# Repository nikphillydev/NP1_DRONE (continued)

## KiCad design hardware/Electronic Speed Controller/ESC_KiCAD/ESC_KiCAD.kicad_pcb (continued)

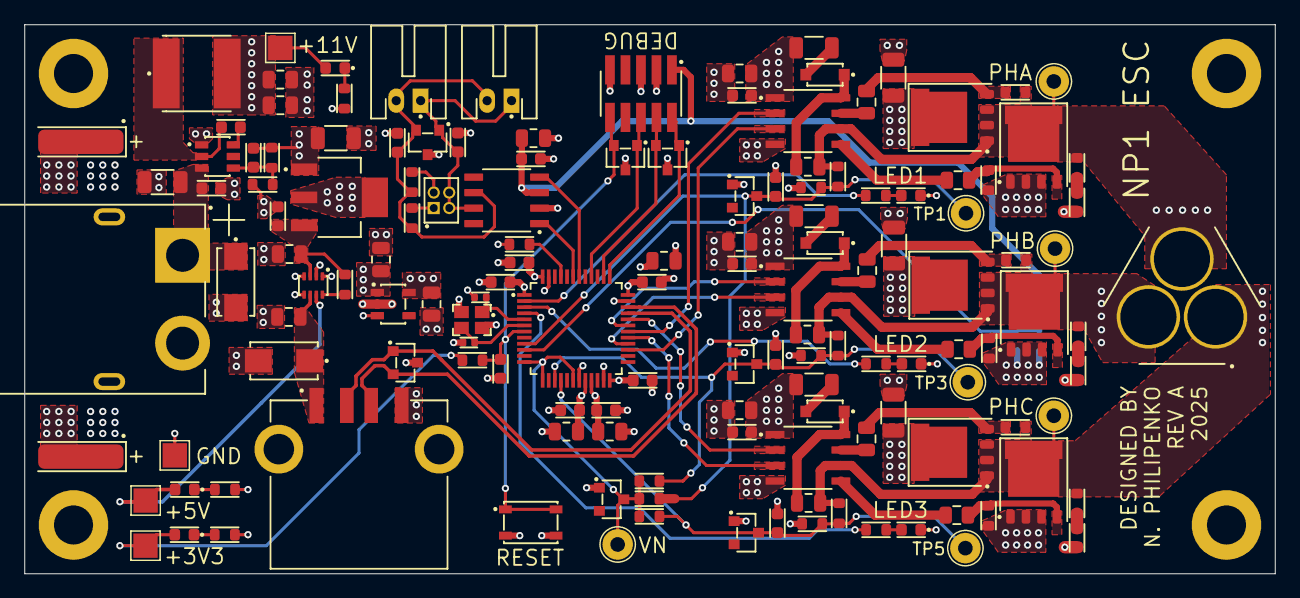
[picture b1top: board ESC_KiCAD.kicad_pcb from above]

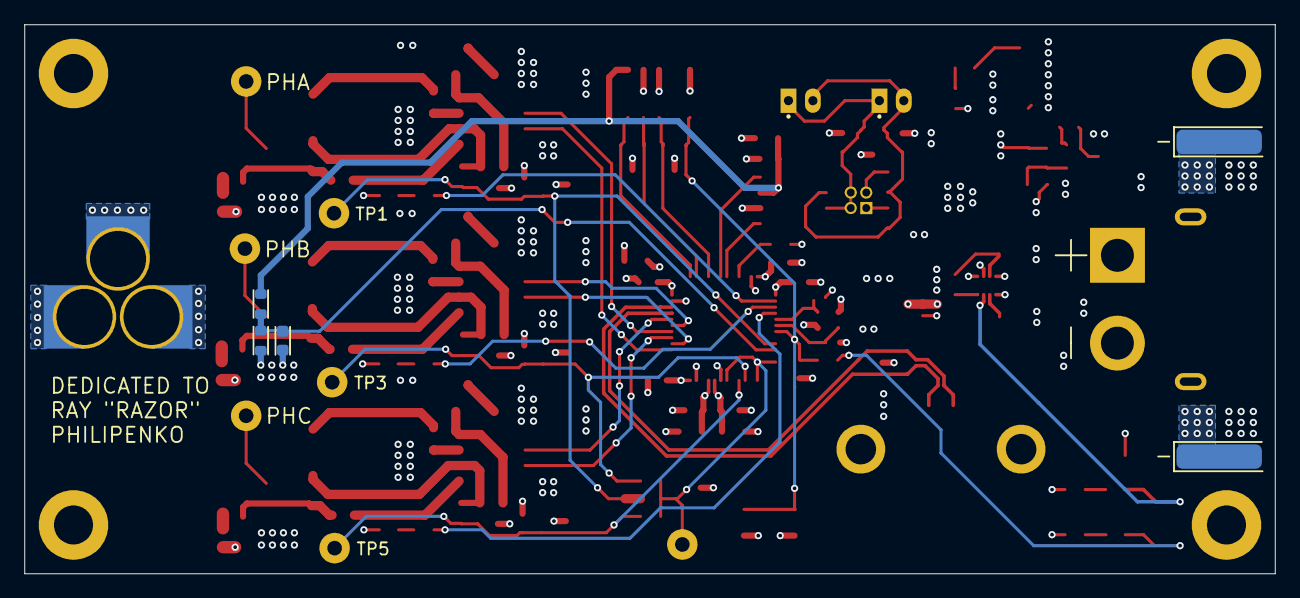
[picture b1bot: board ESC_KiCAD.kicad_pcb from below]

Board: 4 copper layers, 102.5 x 45.0 mm, 150 parts (3 on the bottom side), 70 nets.

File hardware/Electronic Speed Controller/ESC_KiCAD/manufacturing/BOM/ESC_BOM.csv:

"Reference","Value","Description","Qty","JLCPCB Part #","Manufacturer","Manufacturer Part #"
"C1,C8,C11,C17,C43","4.7uF","CAP CER 4.7UF 25V X5R 0805","5","C1779","Samsung Electro-Mechanics","CL21A475KAQNNNE"
"C2,C9,C12,C18,C27,C28,C31,C39,C42,C44,C45,C47,C49","100nF","CAP CER 0.1UF 50V X7R 0603","13","C14663","YAGEO","CC0603KRX7R9BB104"
"C3,C13,C19,C29,C30,C33,C36,C38,C40","1uF","CAP CER 1UF 50V X7R 0805","9","C28323","Samsung Electro-Mechanics","CL21B105KBFNNNE"
"C4,C5","47pF","CAP CER 47PF 50V C0G/NP0 0603","2","C1671","Samsung Electro-Mechanics","CL10C470JB8NNNC"
"C6,C14,C20,C23,C26","10uF","CAP CER 10UF 50V X5R 1206","5","C13585","Samsung Electro-Mechanics","CL31A106KBHNNNE"
"C7,C15,C21","1nF","CAP CER 1000PF 50V X7R 0603","3","C1588","Samsung Electro-Mechanics","CL10B102KB8NNNC"
"C10,C16,C22,C37,C41","10nF","CAP CER 10000PF 50V X7R 0603","5","C57112","Samsung Electro-Mechanics","CL10B103KB8NNNC"
"C24,C25","330uF","CAP ALUM 330UF 20% 35V RADIAL TH","2","C75177","Rubycon","35ZLH330MEFC10X12.5"
"C32","100pF","CAP CER 100PF 50V C0G/NP0 0603","1","C14858","Samsung Electro-Mechanics","CL10C101JB8NNNC"
"C34,C35","22uF","CAP CER 22UF 25V X5R 0805","2","C45783","Samsung Electro-Mechanics","CL21A226MAYNNNE"
"C46,C48","11pF","CAP CER 11PF 50V C0G/NP0 0402","2","C710643","Murata Electronics","GCM1555C1H110JA16D"
"D1,D6,D10","MBR0580S1-7","DIODE SCHOTTKY 80V 500MA SOD123","3","C177047","Diodes Incorporated","MBR0580S1-7"
"D2,D16,D20,D21","D1213A-02SOL-7","TVS DIODE 3.3VWM 10VC SOT233","4","C460585","Diodes Incorporated","D1213A-02SOL-7"
"D3,D4,D7,D8,D11,D12","TPH1R306P1,L1Q","MOSFET N-CH 60V 100A 8SOP","6","C6290261","Toshiba Semiconductor and Storage","TPH1R306P1,L1Q"
"D5,D9,D13,D22","BZX84C3V3-7-F","DIODE ZENER 3.3V 300MW SOT23-3","4","C177019","Diodes Incorporated","BZX84C3V3-7-F"
"D14,D15","SMAJ28CA","TVS DIODE 28VWM 45.4VC DO214AC","2","C148228","Littelfuse Inc.","SMAJ28CA"
"D17,D18,D19,D23,D24,D25","LED","LED YELLOW CLEAR 0603 SMD","6","C72038","Everlight Electronics Co Ltd","EAST16086YA4"
"J1,J2","S2B-PH-K-S","CONN HEADER R/A 2POS 2MM","2","C173752","JST Sales America Inc.","S2B-PH-K-S"
"J3","2x2-1.27MM","CONN HEADER VERT 4POS 1.27MM","1","C18197867","Sullins Connector Solutions","GRPB022VWVN-RC"
"J4","XT60PW-M","XT60 HORIZONTAL 2-PIN POWER","1","C98732","Changzhou Amass Elec","XT60PW-M"
"J5","USB TYPE-A","CONN RCPT USB2.0 TYPEA 4P SMD RA","1","C599118","Amphenol ICC (FCI)","87583-2010BLF"
"J6","2x5-1.27MM","CONN HEADER SMD 10POS 1.27MM","1","C150517","Amphenol ICC (FCI)","20021121-00010C4LF"
"J7","MT60-F","MT60 VERT 3-PIN POWER","1","C40020701","Amass Electronics","MT60-F"
"L1","15uH","FIXED IND 15UH 2.05A 88MOHM SMD","1","C83374","Shenzhen Sunlord Electronics Co., Ltd.","SWPA6045S150MT"
"R1,R11,R19","2.2R","RES SMD 2.2 OHM 1% 3/4W 1206","3","C1854860","Vishay Dale","CRCW12062R20FKEAHP"
"R2,R3,R12,R13,R20,R21","10R/250mW","RES 10 OHM 1% 1/4W 0805","6","C727983","YAGEO","AC0805FR-7W10RL"
"R4,R5,R9,R14,R15,R17,R22,R23,R25,R27,R34,R35","10k","RES 10K OHM 1% 1/10W 0603","12","C25804","Stackpole Electronics Inc","RMCF0603FT10K0"
"R6,R7","120R","RES 120 OHM 1% 1/10W 0603","2","C22787","YAGEO","RC0603FR-07120RL"
"R8,R16,R24,R37,R38,R39","68k","RES SMD 68K OHM 1% 1/10W 0603","6","C23231","Panasonic Electronic Components","ERJ-3EKF6802V"
"R10,R18,R26","10R","RES 10 OHM 1% 1/10W 0603","3","C22859","YAGEO","RC0603FR-0710RL"
"R28","100k","RES 100K OHM 1% 1/10W 0603","1","C25803","YAGEO","RC0603FR-07100KL"
"R29,R31","5.76k","RES 5.76K OHM 1% 1/10W 0603","2","C2933239","YAGEO","RC0603FR-075K76L"
"R30","4.7k","RES 4.7K OHM 1% 1/10W 0603","1","C23162","YAGEO","RC0603FR-074K7L"
"R32","3k","RES 3K OHM 1% 1/10W 0603","1","C4211","Stackpole Electronics Inc","RMCF0603FT3K00"
"R33,R36,R40,R41","1k","RES 1K OHM 1% 1/10W 0603","4","C21190","Stackpole Electronics Inc","RMCF0603FT1K00"
"S1","SKRPARE010","TACT SWITCHTTM","1","C341730","Alps Alpine","SKRPARE010"
"TH1","NTC 10k","THERMISTOR NTC 10KOHM 3380K 0603","1","C440252","Murata Electronics","NCU18XH103F60RB"
"U1,U3,U4","IRS21867STRPBF","IC GATE DRVR HALF-BRIDGE 8SOIC","3","C52290","Infineon Technologies","IRS21867STRPBF"
"U2","SN65HVD232DR","IC TRANSCEIVER HALF 1/1 8SOIC","1","C30530","Texas Instruments","SN65HVD232DR"
"U5","LM7805MPX/NOPB","IC REG LINEAR 5V 1.5A SOT-223-4","1","C2848241","Texas Instruments","LM7805MPX/NOPB"
"U6","TPS54302DDCR","IC REG BUCK ADJ 3A SOT23","1","C311983","Texas Instruments","TPS54302DDCR"
"U7","LM66200DRLR","IC POWER OR CONTROLLER","1","C3235556","Texas Instruments","LM66200DRLR"
"U8","TLV75533PDBVR","IC REG LINEAR 3.3V 500MA SOT23-5","1","C404027","Texas Instruments","TLV75533PDBVR"
"U9","STM32G474CET6","IC MCU 32BIT 512KB FLASH 48LQFP","1","C730125","STMicroelectronics","STM32G474CET6"
"X1","NX2520SA-16MHz","CRYSTAL 16.0000MHZ 8PF SMD","1","C280836","NDK (NIHON DEMPA KOGYO CO., LTD)","STDCSW5-16M"

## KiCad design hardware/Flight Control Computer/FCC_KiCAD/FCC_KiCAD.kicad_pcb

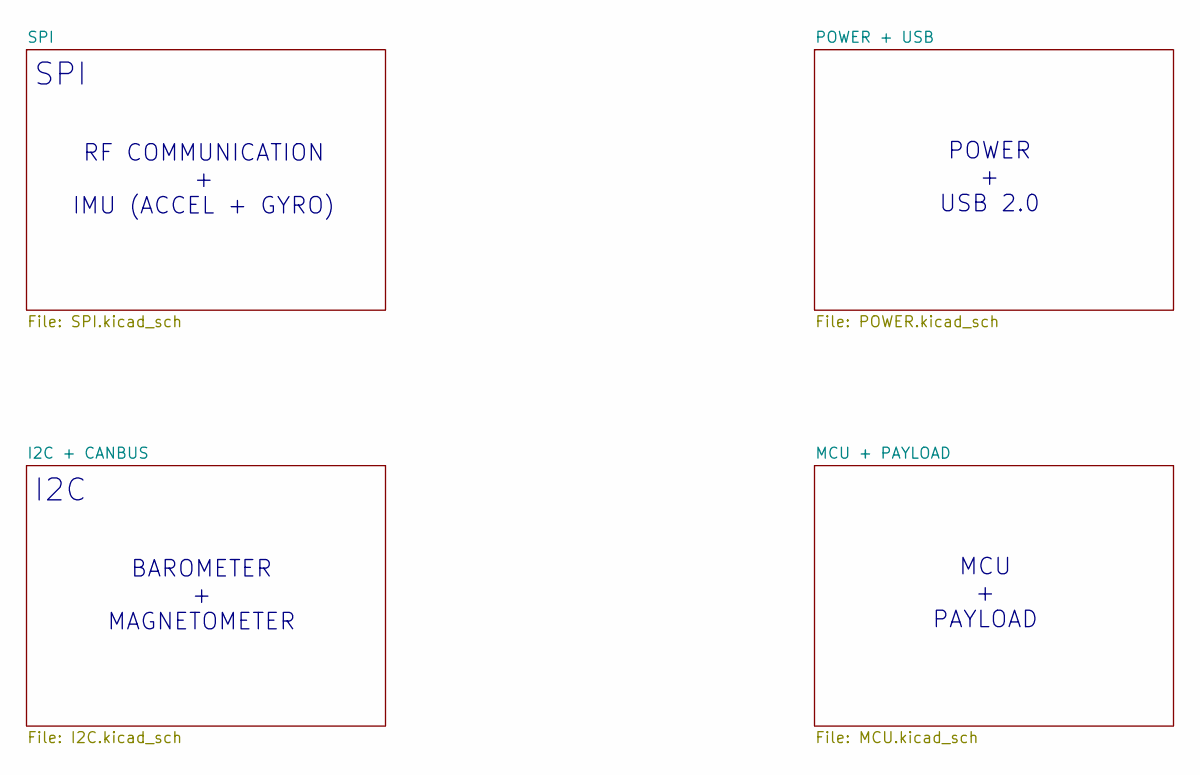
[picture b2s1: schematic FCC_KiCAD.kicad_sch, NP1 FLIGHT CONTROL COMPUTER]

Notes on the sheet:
MCU + PAYLOAD
BAROMETER + MAGNETOMETER
SPI
POWER + USB 2.0
RF COMMUNICATION + IMU (ACCEL + GYRO)
I2C

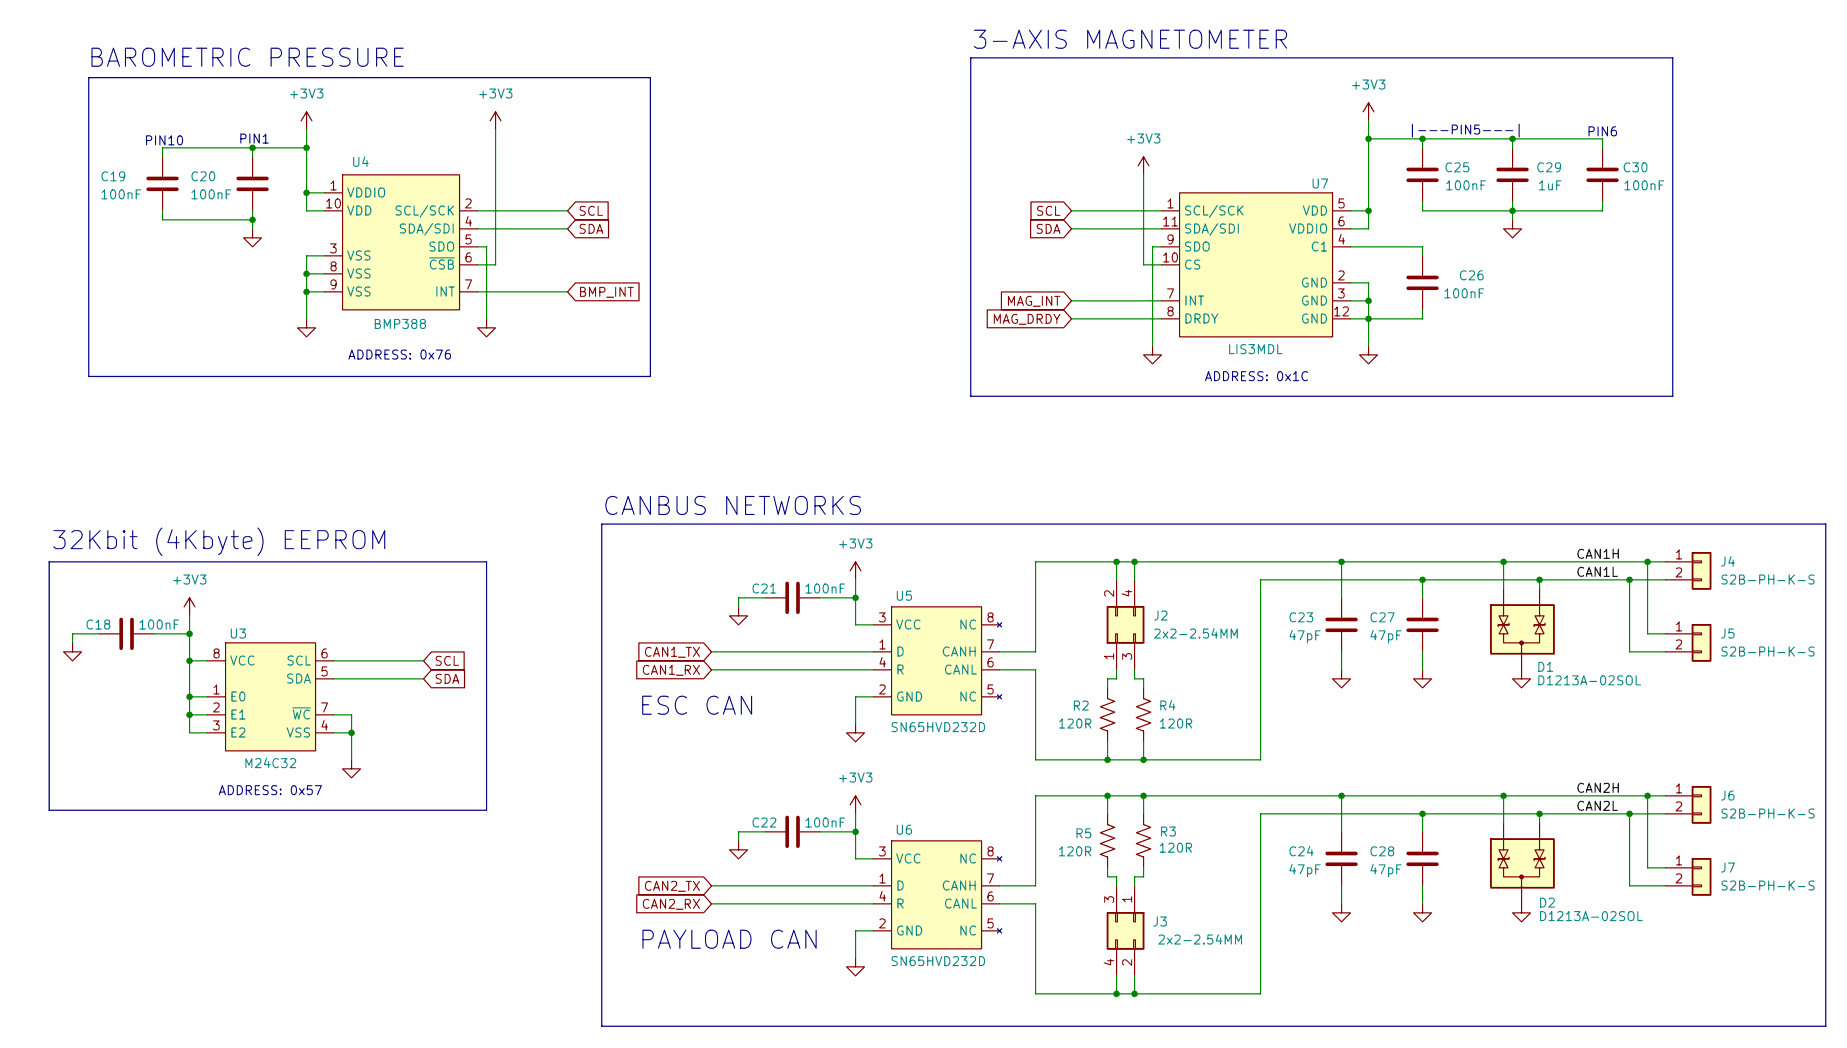
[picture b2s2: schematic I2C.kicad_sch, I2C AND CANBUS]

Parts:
C18, C19, C20, C21, C22, C25, C26, C30: 100nF; CAP_0402_1005Metric; JLCPCB Part# C77020
C23, C24, C27, C28: 47pF; CAP_0402_1005Metric; JLCPCB Part# C76970
C29: 1uF; CAP_0402_1005Metric; JLCPCB Part# C77009
D1, D2: D1213A-02SOL; DiodesINC_SOT23-3; JLCPCB Part# C460585
J2, J3: 2x2-2.54MM; CONN_MALE_TH_2.54MM_2x2; JLCPCB Part# C66690
J4, J5, J6, J7: S2B-PH-K-S; CONN_JST_S2B-PH-K-S; JLCPCB Part# C173752
R2, R3, R4, R5: 120R; RES_0603_1608Metric; JLCPCB Part# C22787
U3: M24C32; STM_SO8N; JLCPCB Part# C79920
U4: BMP388; BOSCH_LGA-10; JLCPCB Part# C779278
U5, U6: SN65HVD232D; TI_SOIC-8; JLCPCB Part# C30530
U7: LIS3MDL; STM_LGA-12L; JLCPCB Part# C478483

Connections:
+3V3: C18.2, C19.1, C20.1, C21.2, C22.2, C25.1, C29.1, C30.1, U3.1 (E0), U3.2 (E1), U3.3 (E2), U3.8 (VCC), U4.1 (VDDIO), U4.6 (~CSB), U4.10 (VDD), U5.3 (VCC), U6.3 (VCC), U7.5 (VDD), U7.6 (VDDIO), U7.10 (CS); also elsewhere on the board
/I2C + CANBUS/CAN1H: C23.1, D1.1 (K), J2.2, J2.4, J4.1, J5.1, U5.7 (CANH)
/I2C + CANBUS/CAN1L: C27.1, D1.2 (K), J4.2, J5.2, R2.2, R4.2, U5.6 (CANL)
/I2C + CANBUS/CAN2H: C24.1, D2.1 (K), J6.1, J7.1, R3.2, R5.2, U6.7 (CANH)
/I2C + CANBUS/CAN2L: C28.1, D2.2 (K), J3.2, J3.4, J6.2, J7.2, U6.6 (CANL)
BMP_INT: U4.7 (INT); also elsewhere on the board
CAN1_RX: U5.4 (R); also elsewhere on the board
CAN1_TX: U5.1 (D); also elsewhere on the board
CAN2_RX: U6.4 (R); also elsewhere on the board
CAN2_TX: U6.1 (D); also elsewhere on the board
GND: C18.1, C19.2, C20.2, C21.1, C22.1, C23.2, C24.2, C25.2, C26.2, C27.2, C28.2, C29.2, C30.2, D1.3 (A), D2.3 (A), U3.4 (VSS), U3.7 (~WC), U4.3 (VSS), U4.5 (SDO), U4.8 (VSS), U4.9 (VSS), U5.2 (GND), U6.2 (GND), U7.2 (GND), U7.3 (GND), U7.9 (SDO), U7.12 (GND); also elsewhere on the board
MAG_DRDY: U7.8 (DRDY); also elsewhere on the board
MAG_INT: U7.7 (INT); also elsewhere on the board
unnamed: J2.1, R2.1
unnamed: J2.3, R4.1
unnamed: J3.1, R3.1
unnamed: J3.3, R5.1
unnamed: C26.1, U7.4 (C1)
SCL: U3.6 (SCL), U4.2 (SCL/SCK), U7.1 (SCL/SCK); also elsewhere on the board
SDA: U3.5 (SDA), U4.4 (SDA/SDI), U7.11 (SDA/SDI); also elsewhere on the board

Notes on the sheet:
ESC CAN
BAROMETRIC PRESSURE
PIN1
|---PIN5---|
3-AXIS MAGNETOMETER
32Kbit (4Kbyte) EEPROM
CANBUS NETWORKS
PIN10
ADDRESS: 0x76
PAYLOAD CAN
ADDRESS: 0x57
PIN6
ADDRESS: 0x1C

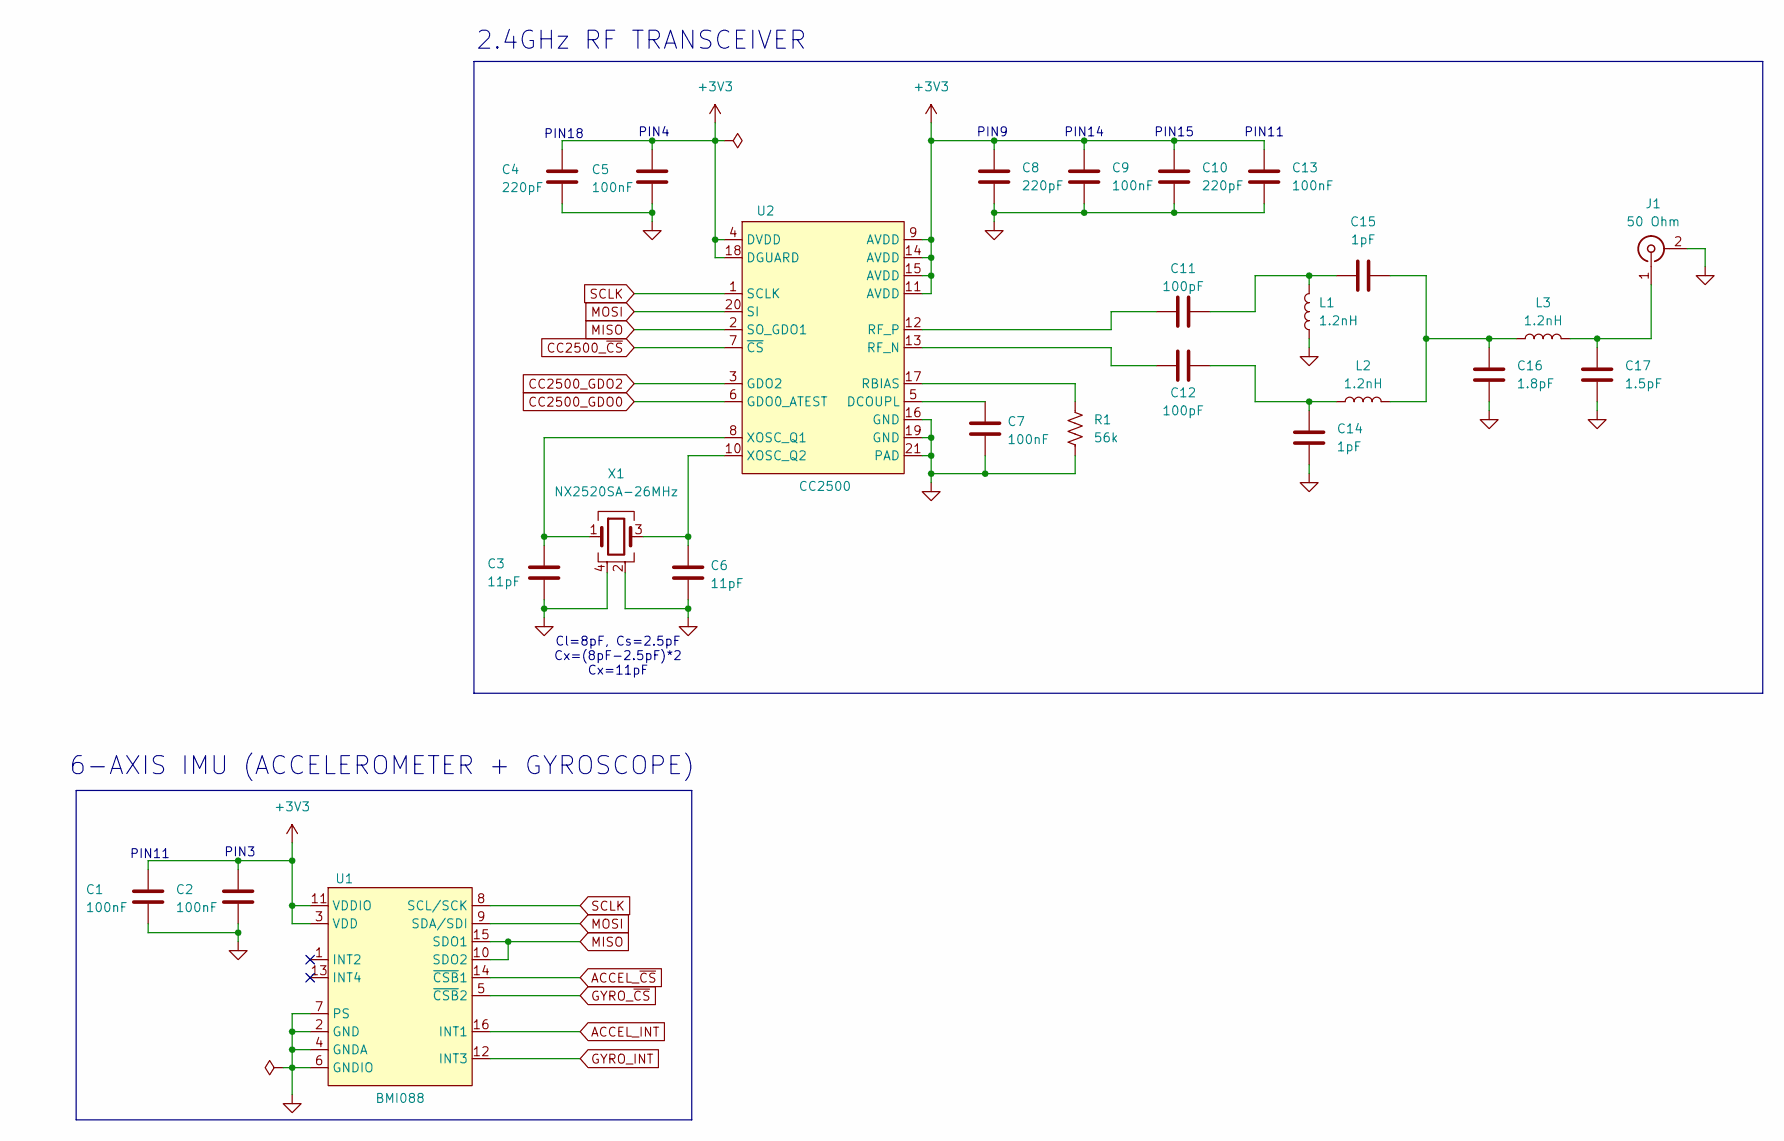
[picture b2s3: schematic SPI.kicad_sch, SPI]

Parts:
C1, C2, C5, C7, C9, C13: 100nF; CAP_0402_1005Metric; JLCPCB Part# C77020
C3, C6: 11pF; CAP_0402_1005Metric; JLCPCB Part# C710643
C4, C8, C10: 220pF; CAP_0402_1005Metric; JLCPCB Part# C97872
C11, C12: 100pF; CAP_0402_1005Metric; JLCPCB Part# C77177
C14, C15: 1pF; CAP_0402_1005Metric; JLCPCB Part# C76953
C16: 1.8pF; CAP_0402_1005Metric; JLCPCB Part# C85878
C17: 1.5pF; CAP_0402_1005Metric; JLCPCB Part# C76958
J1: 50 Ohm; RF-SMA_Dosinconn_DOSIN-806-0001; JLCPCB Part# C521220
L1, L2, L3: 1.2nH; L_0402_1005Metric; JLCPCB Part# C77105
R1: 56k; RES_0603_1608Metric; JLCPCB Part# C144110
U1: BMI088; BOSCH_LGA-16; JLCPCB Part# C194919
U2: CC2500; TI_QFN-20; JLCPCB Part# C57494
X1: NX2520SA-26MHz; NDK_NX2520SA; JLCPCB Part# C910046

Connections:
+3V3: C1.1, C2.1, C4.1, C5.1, C8.1, C9.1, C10.1, C13.1, U1.3 (VDD), U1.11 (VDDIO), U2.4 (DVDD), U2.9 (AVDD), U2.11 (AVDD), U2.14 (AVDD), U2.15 (AVDD), U2.18 (DGUARD); also elsewhere on the board
ACCEL_INT: U1.16 (INT1); also elsewhere on the board
ACCEL_~CS: U1.14 (~CSB1); also elsewhere on the board
CC2500_GDO0: U2.6 (GDO0_ATEST); also elsewhere on the board
CC2500_GDO2: U2.3 (GDO2); also elsewhere on the board
CC2500_~CS: U2.7 (~CS); also elsewhere on the board
GND: C1.2, C2.2, C3.2, C4.2, C5.2, C6.2, C7.2, C8.2, C9.2, C10.2, C13.2, C14.2, C16.2, C17.2, J1.2 (Ext), L1.1, R1.2, U1.2 (GND), U1.4 (GNDA), U1.6 (GNDIO), U1.7 (PS), U2.16 (GND), U2.19 (GND), U2.21 (PAD), X1.2, X1.4; also elsewhere on the board
GYRO_INT: U1.12 (INT3); also elsewhere on the board
GYRO_~CS: U1.5 (~CSB2); also elsewhere on the board
MISO: U1.10 (SDO2), U1.15 (SDO1), U2.2 (SO_GDO1); also elsewhere on the board
MOSI: U1.9 (SDA/SDI), U2.20 (SI); also elsewhere on the board
unnamed: C11.2, C15.1, L1.2
unnamed: C12.2, C14.1, L2.1
unnamed: C15.2, C16.1, L2.2, L3.1
unnamed: C17.1, J1.1 (In), L3.2
unnamed: C7.1, U2.5 (DCOUPL)
unnamed: R1.1, U2.17 (RBIAS)
unnamed: C12.1, U2.13 (RF_N)
unnamed: C11.1, U2.12 (RF_P)
unnamed: C3.1, U2.8 (XOSC_Q1), X1.1
unnamed: C6.1, U2.10 (XOSC_Q2), X1.3
SCLK: U1.8 (SCL/SCK), U2.1 (SCLK); also elsewhere on the board

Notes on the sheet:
2.4GHz RF TRANSCEIVER
PIN11
PIN4
PIN18
PIN14
6-AXIS IMU (ACCELEROMETER + GYROSCOPE)
PIN9
PIN3
Cl=8pF, Cs=2.5pF Cx=(8pF-2.5pF)*2 Cx=11pF
PIN15

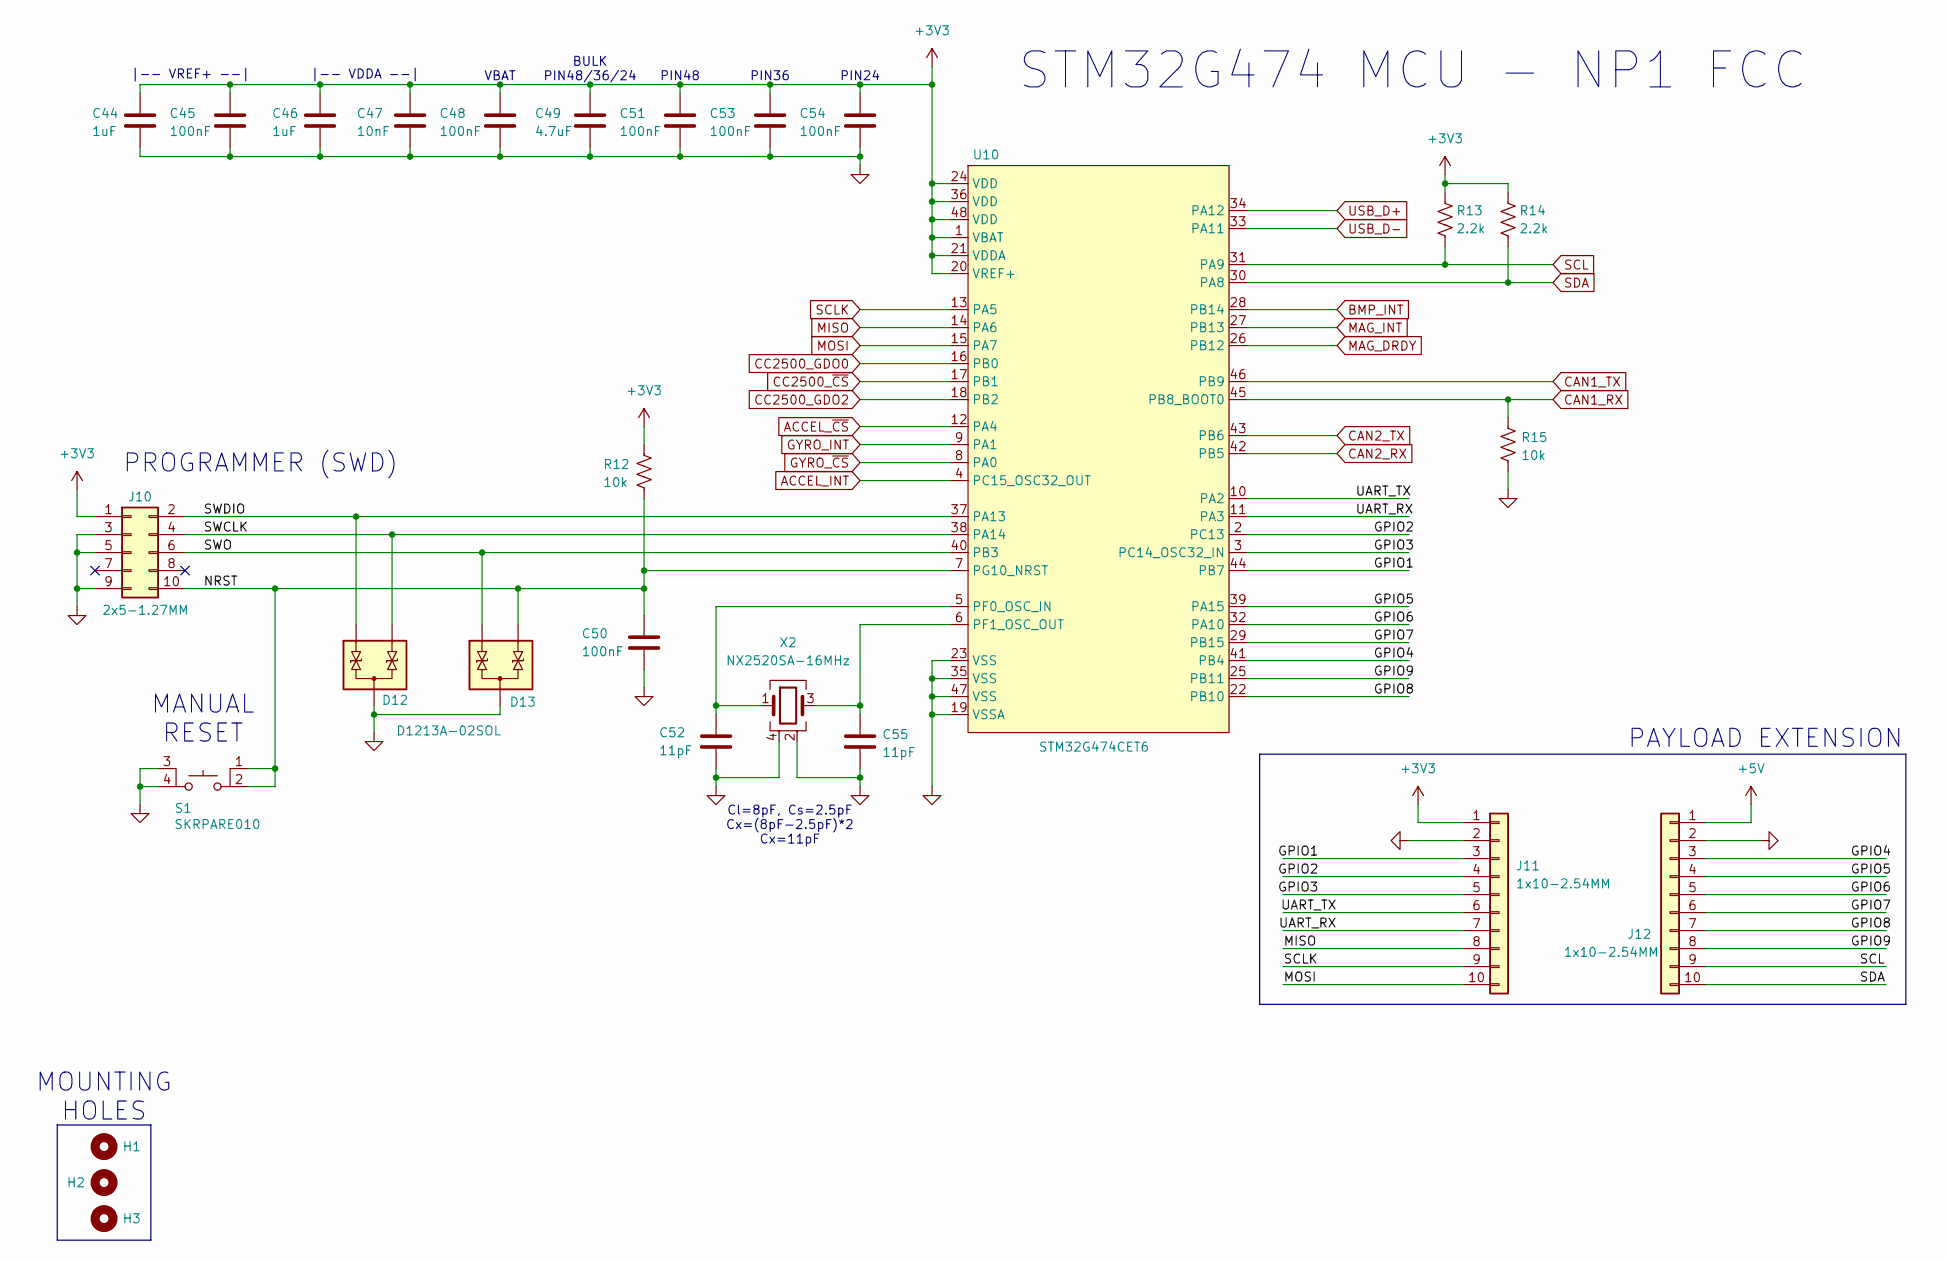
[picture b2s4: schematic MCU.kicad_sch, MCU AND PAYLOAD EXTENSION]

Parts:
C44, C46: 1uF; CAP_0402_1005Metric; JLCPCB Part# C77009
C45, C48, C50, C51, C53, C54: 100nF; CAP_0402_1005Metric; JLCPCB Part# C77020
C47: 10nF; CAP_0402_1005Metric; JLCPCB Part# C162190
C49: 4.7uF; CAP_0402_1005Metric; JLCPCB Part# C77004
C52, C55: 11pF; CAP_0402_1005Metric; JLCPCB Part# C710643
D12, D13: D1213A-02SOL; DiodesINC_SOT23-3; JLCPCB Part# C460585
H1, H2, H3: MountingHole; MountingHole_2.2mm_M2_Pad
J10: 2x5-1.27MM; CONN_MALE_SMT_1.27MM_2x5; JLCPCB Part# C150517
J11, J12: 1x10-2.54MM; CONN_FEMALE_TH_2.54MM_1x10; JLCPCB Part# C2897373
R12, R15: 10k; RES_0603_1608Metric; JLCPCB Part# C98220
R13, R14: 2.2k; RES_0603_1608Metric; JLCPCB Part# C114662
S1: SKRPARE010; TACT_SKRP; JLCPCB Part# C341730
U10: STM32G474CET6; STM_LQFP48; JLCPCB Part# C730125
X2: NX2520SA-16MHz; NDK_NX2520SA; JLCPCB Part# C280836

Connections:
+3V3: C44.1, C45.1, C46.1, C47.1, C48.1, C49.1, C51.1, C53.1, C54.1, J10.1, J11.1, R12.1, R13.1, R14.1, U10.1 (VBAT), U10.20 (VREF+), U10.21 (VDDA), U10.24 (VDD), U10.36 (VDD), U10.48 (VDD); also elsewhere on the board
+5V: J12.1; also elsewhere on the board
/MCU + PAYLOAD/GPIO1: J11.3, U10.44 (PB7)
/MCU + PAYLOAD/GPIO2: J11.4, U10.2 (PC13)
/MCU + PAYLOAD/GPIO3: J11.5, U10.3 (PC14_OSC32_IN)
/MCU + PAYLOAD/GPIO4: J12.3, U10.41 (PB4)
/MCU + PAYLOAD/GPIO5: J12.4, U10.39 (PA15)
/MCU + PAYLOAD/GPIO6: J12.5, U10.32 (PA10)
/MCU + PAYLOAD/GPIO7: J12.6, U10.29 (PB15)
/MCU + PAYLOAD/GPIO8: J12.7, U10.22 (PB10)
/MCU + PAYLOAD/GPIO9: J12.8, U10.25 (PB11)
/MCU + PAYLOAD/NRST: C50.1, D13.2 (K), J10.10, R12.2, S1.1, S1.2, U10.7 (PG10_NRST)
/MCU + PAYLOAD/SWCLK: D12.2 (K), J10.4, U10.38 (PA14)
/MCU + PAYLOAD/SWDIO: D12.1 (K), J10.2, U10.37 (PA13)
/MCU + PAYLOAD/SWO: D13.1 (K), J10.6, U10.40 (PB3)
/MCU + PAYLOAD/UART_RX: J11.7, U10.11 (PA3)
/MCU + PAYLOAD/UART_TX: J11.6, U10.10 (PA2)
ACCEL_INT: U10.4 (PC15_OSC32_OUT); also elsewhere on the board
ACCEL_~CS: U10.12 (PA4); also elsewhere on the board
BMP_INT: U10.28 (PB14); also elsewhere on the board
CAN1_RX: R15.1, U10.45 (PB8_BOOT0); also elsewhere on the board
CAN1_TX: U10.46 (PB9); also elsewhere on the board
CAN2_RX: U10.42 (PB5); also elsewhere on the board
CAN2_TX: U10.43 (PB6); also elsewhere on the board
CC2500_GDO0: U10.16 (PB0); also elsewhere on the board
CC2500_GDO2: U10.18 (PB2); also elsewhere on the board
CC2500_~CS: U10.17 (PB1); also elsewhere on the board
GND: C44.2, C45.2, C46.2, C47.2, C48.2, C49.2, C50.2, C51.2, C52.2, C53.2, C54.2, C55.2, D12.3 (A), D13.3 (A), J10.3, J10.5, J10.9, J11.2, J12.2, R15.2, S1.3, S1.4, U10.19 (VSSA), U10.23 (VSS), U10.35 (VSS), U10.47 (VSS), X2.2, X2.4; also elsewhere on the board
GYRO_INT: U10.9 (PA1); also elsewhere on the board
GYRO_~CS: U10.8 (PA0); also elsewhere on the board
MAG_DRDY: U10.26 (PB12); also elsewhere on the board
MAG_INT: U10.27 (PB13); also elsewhere on the board
MISO: J11.8, U10.14 (PA6); also elsewhere on the board
MOSI: J11.10, U10.15 (PA7); also elsewhere on the board
unnamed: C52.1, U10.5 (PF0_OSC_IN), X2.1
unnamed: C55.1, U10.6 (PF1_OSC_OUT), X2.3
SCL: J12.9, R13.2, U10.31 (PA9); also elsewhere on the board
SCLK: J11.9, U10.13 (PA5); also elsewhere on the board
SDA: J12.10, R14.2, U10.30 (PA8); also elsewhere on the board
USB_D+: U10.34 (PA12); also elsewhere on the board
USB_D-: U10.33 (PA11); also elsewhere on the board

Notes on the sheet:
PAYLOAD EXTENSION
STM32G474 MCU - NP1 FCC
MOUNTING HOLES
PIN48
VBAT
|-- VREF+ --|
|-- VDDA --|
PROGRAMMER (SWD)
Cl=8pF, Cs=2.5pF Cx=(8pF-2.5pF)*2 Cx=11pF
PIN24
BULK PIN48/36/24
MANUAL RESET
PIN36

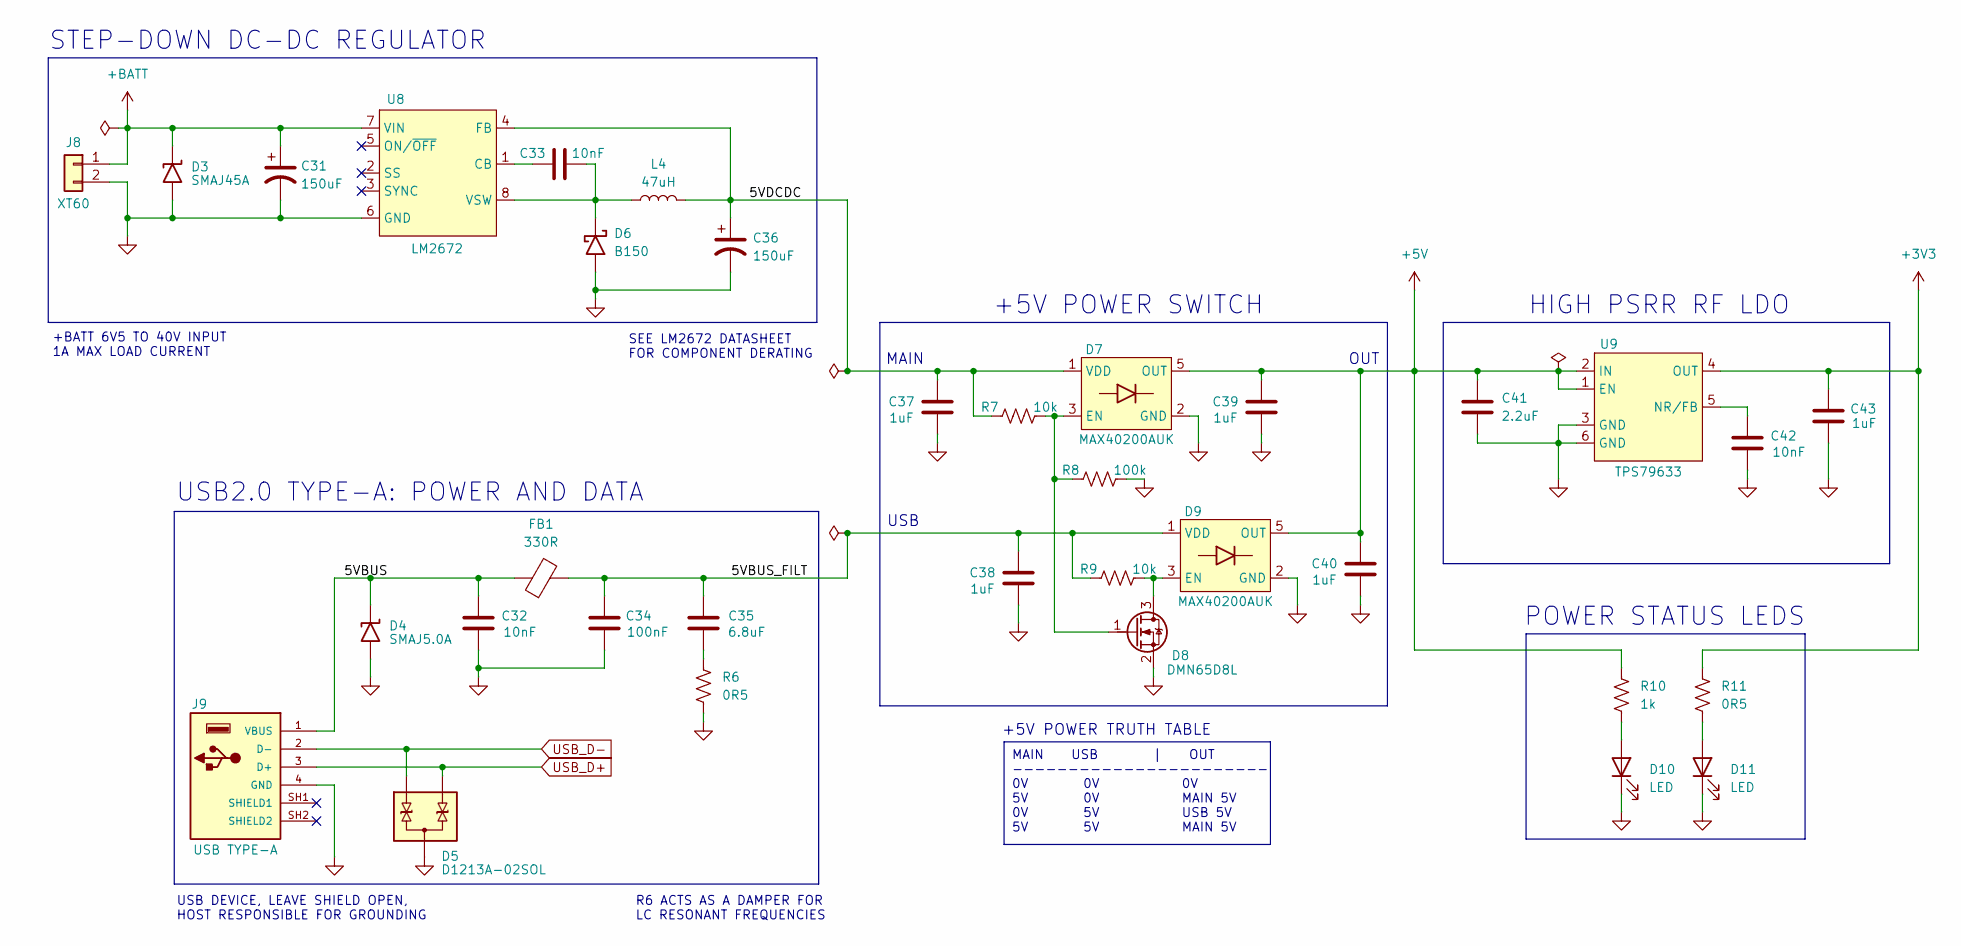
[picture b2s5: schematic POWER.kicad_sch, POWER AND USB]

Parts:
C31, C36: 150uF; NICHICON_UHE_10x12.5; JLCPCB Part# C116230
C32, C33, C42: 10nF; CAP_0402_1005Metric; JLCPCB Part# C162190
C34: 100nF; CAP_0402_1005Metric; JLCPCB Part# C77020
C35: 6.8uF; CAP_0603_1608Metric; JLCPCB Part# C338096
C37, C38, C39, C40, C43: 1uF; CAP_0402_1005Metric; JLCPCB Part# C77009
C41: 2.2uF; CAP_0402_1005Metric; JLCPCB Part# C385032
D3: SMAJ45A; DiodesINC_SMA; JLCPCB Part# C134989
D4: SMAJ5.0A; DiodesINC_SMA; JLCPCB Part# C87074
D5: D1213A-02SOL; DiodesINC_SOT23-3; JLCPCB Part# C460585
D6: B150; DiodesINC_SMA; JLCPCB Part# C134431
D7, D9: MAX40200AUK; AnalogDevices_SOT23-5; JLCPCB Part# C2649430
D8: DMN65D8L; DiodesINC_SOT23-3; JLCPCB Part# C155341
D10, D11: LED; LED_0603_1608Metric; JLCPCB Part# C72038
FB1: 330R; L_0603_1608Metric; JLCPCB Part# C710391
J8: XT60; CONN_MALE_TH_XT60; JLCPCB Part# C98733
J9: USB TYPE-A; USB2.0_4P_AMPHENOL_87583-2010BLF; JLCPCB Part# C599118
L4: 47uH; TDK_CLF7045-D; JLCPCB Part# C432960
R6, R11: 0R5; RES_0603_1608Metric; JLCPCB Part# C309622
R7, R9: 10k; RES_0603_1608Metric; JLCPCB Part# C98220
R8: 100k; RES_0603_1608Metric; JLCPCB Part# C14675
R10: 1k; RES_0603_1608Metric; JLCPCB Part# C22548
U8: LM2672; TI_SOIC-8; JLCPCB Part# C180371
U9: TPS79633; TI_SOT223-6; JLCPCB Part# C485803

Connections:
+3V3: C43.2, R11.1, U9.4 (OUT); also elsewhere on the board
+5V: C39.2, C40.2, C41.1, D7.5 (OUT), D9.5 (OUT), R10.1, U9.1 (EN), U9.2 (IN); also elsewhere on the board
+BATT: C31.1, D3.1 (K), J8.1, U8.7 (VIN)
/POWER + USB/5VBUS: C32.2, D4.1 (K), FB1.1, J9.1 (VBUS)
/POWER + USB/5VBUS_FILT: C34.2, C35.2, C38.2, D9.1 (VDD), FB1.2, R9.1
/POWER + USB/5VDCDC: C36.1, C37.2, D7.1 (VDD), L4.2, R7.1, U8.4 (FB)
GND: C31.2, C32.1, C34.1, C36.2, C37.1, C38.1, C39.1, C40.1, C41.2, C42.1, C43.1, D3.2 (A), D4.2 (A), D5.3 (A), D6.2 (A), D7.2 (GND), D8.2 (S), D9.2 (GND), D10.1 (K), D11.1 (K), J8.2, J9.4 (GND), R6.2, R8.2, U8.6 (GND), U9.3 (GND), U9.6 (GND); also elsewhere on the board
unnamed: C35.1, R6.1
unnamed: C33.2, D6.1 (K), L4.1, U8.8 (VSW)
unnamed: D7.3 (EN), D8.1 (G), R7.2, R8.1
unnamed: D8.3 (D), D9.3 (EN), R9.2
unnamed: D10.2 (A), R10.2
unnamed: D11.2 (A), R11.2
unnamed: C33.1, U8.1 (CB)
unnamed: C42.2, U9.5 (NR/FB)
USB_D+: D5.2 (K), J9.3 (D+); also elsewhere on the board
USB_D-: D5.1 (K), J9.2 (D-); also elsewhere on the board

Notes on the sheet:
MAIN USB | OUT ----------------------- 0V 0V 0V 5V 0V MAIN 5V 0V 5V USB 5V 5V 5V MAIN 5V
POWER STATUS LEDS
USB DEVICE, LEAVE SHIELD OPEN, HOST RESPONSIBLE FOR GROUNDING
USB2.0 TYPE-A: POWER AND DATA
USB
+5V POWER SWITCH
HIGH PSRR RF LDO
R6 ACTS AS A DAMPER FOR LC RESONANT FREQUENCIES
+5V POWER TRUTH TABLE
STEP-DOWN DC-DC REGULATOR
SEE LM2672 DATASHEET FOR COMPONENT DERATING
MAIN
+BATT 6V5 TO 40V INPUT 1A MAX LOAD CURRENT
OUT

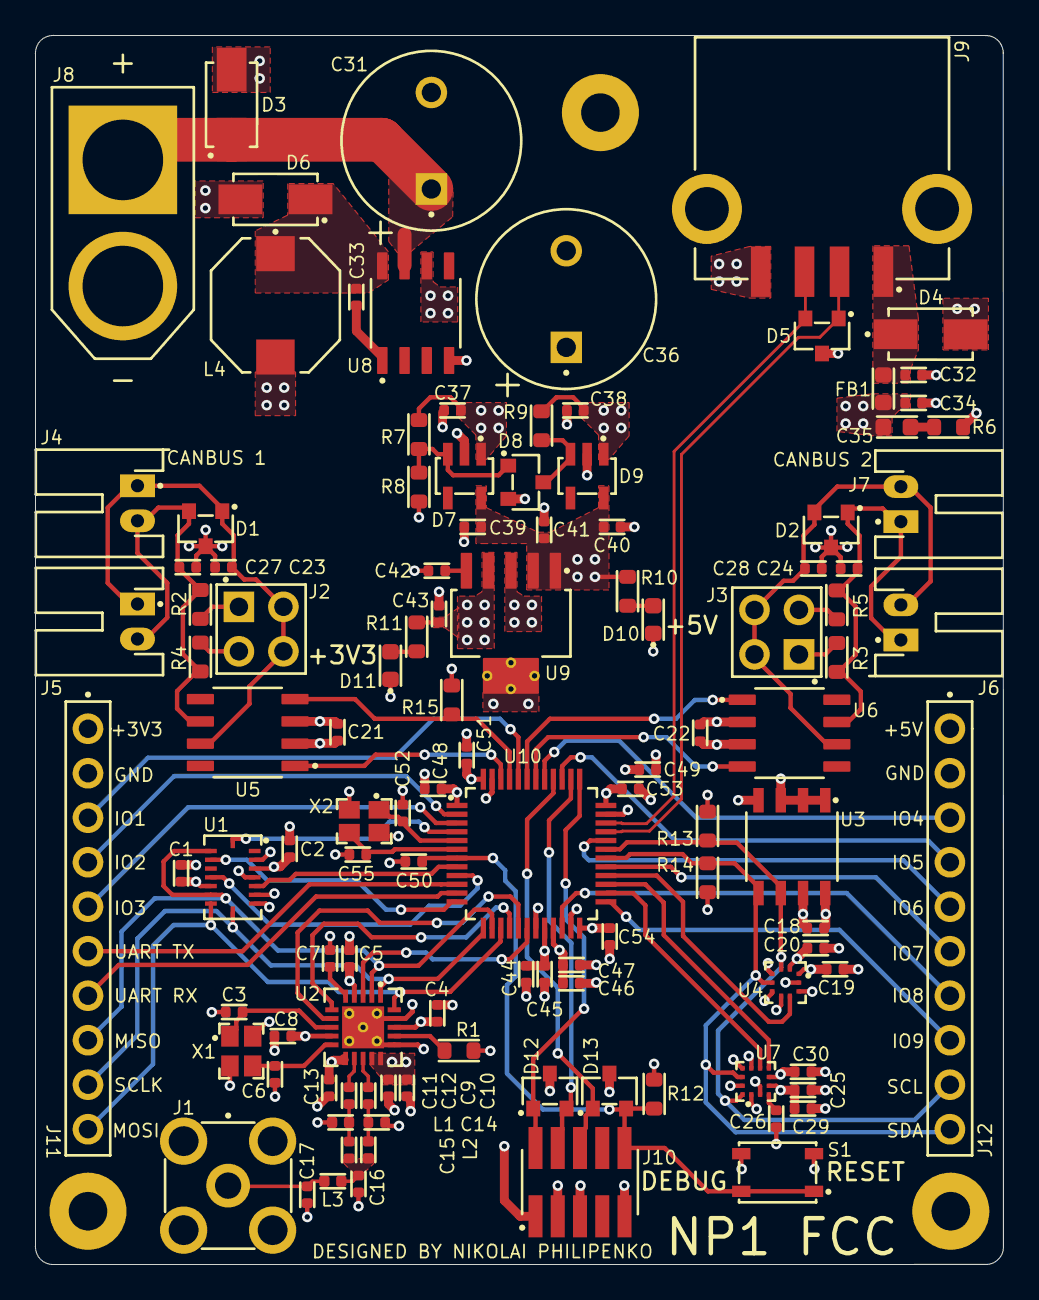
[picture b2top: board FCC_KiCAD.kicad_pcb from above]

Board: 4 copper layers, 55.3 x 70.2 mm, 116 parts (0 on the bottom side), 72 nets.

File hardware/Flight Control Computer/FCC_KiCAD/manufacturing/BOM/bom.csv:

Comment,Designator,Footprint,JLCPCB Part#
100nF,"C1,C2,C5,C7,C9,C13,C18,C19,C20,C21,C22,C25,C26,C30,C34,C45,C48,C50,C51,C53,C54",Capacitors:CAP_0402_1005Metric,C77020
11pF,"C3,C6,C52,C55",Capacitors:CAP_0402_1005Metric,C710643
220pF,"C4,C8,C10",Capacitors:CAP_0402_1005Metric,C97872
100pF,"C11,C12",Capacitors:CAP_0402_1005Metric,C77177
1pF,"C14,C15",Capacitors:CAP_0402_1005Metric,C76953
1.8pF,C16,Capacitors:CAP_0402_1005Metric,C85878
1.5pF,C17,Capacitors:CAP_0402_1005Metric,C76958
47pF,"C23,C24,C27,C28",Capacitors:CAP_0402_1005Metric,C76970
1uF,"C29,C37,C38,C39,C40,C43,C44,C46",Capacitors:CAP_0402_1005Metric,C77009
150uF,"C31,C36",Capacitors:NICHICON_UHE_10x12.5,C116230
10nF,"C32,C33,C42,C47",Capacitors:CAP_0402_1005Metric,C162190
6.8uF,C35,Capacitors:CAP_0603_1608Metric,C338096
2.2uF,C41,Capacitors:CAP_0402_1005Metric,C385032
4.7uF,C49,Capacitors:CAP_0402_1005Metric,C77004
D1213A-02SOL,"D1,D2,D5,D12,D13",Diodes:DiodesINC_SOT23-3,C460585
SMAJ45A,D3,Diodes:DiodesINC_SMA,C134989
SMAJ5.0A,D4,Diodes:DiodesINC_SMA,C87074
B150,D6,Diodes:DiodesINC_SMA,C134431
MAX40200AUK,"D7,D9",Diodes:AnalogDevices_SOT23-5,C2649430
DMN65D8L,D8,Diodes:DiodesINC_SOT23-3,C155341
LED,"D10,D11",Diodes:LED_0603_1608Metric,C72038
330R,FB1,Inductors:L_0603_1608Metric,C710391
50 Ohm,J1,Connectors:RF-SMA_Dosinconn_DOSIN-806-0001,C521220
2x2-2.54MM ,"J2,J3",Connectors:CONN_MALE_TH_2.54MM_2x2,C66690
S2B-PH-K-S,"J4,J5,J6,J7",Connectors:CONN_JST_S2B-PH-K-S,C173752
XT60,J8,Connectors:CONN_MALE_TH_XT60,C98733
USB TYPE-A,J9,Connectors:USB2.0_4P_AMPHENOL_87583-2010BLF,C599118
2x5-1.27MM,J10,Connectors:CONN_MALE_SMT_1.27MM_2x5,C150517
1x10-2.54MM ,"J11,J12",Connectors:CONN_FEMALE_TH_2.54MM_1x10,C2897373
1.2nH,"L1,L2,L3",Inductors:L_0402_1005Metric,C77105
47uH,L4,Inductors:TDK_CLF7045-D,C432960
56k,R1,Resistors:RES_0603_1608Metric,C144110
120R,"R2,R3,R4,R5",Resistors:RES_0603_1608Metric,C22787
0R5,"R6,R11",Resistors:RES_0603_1608Metric,C309622
10k,"R7,R9,R12,R15",Resistors:RES_0603_1608Metric,C98220
100k,R8,Resistors:RES_0603_1608Metric,C14675
1k,R10,Resistors:RES_0603_1608Metric,C22548
2.2k,"R13,R14",Resistors:RES_0603_1608Metric,C114662
SKRPARE010,S1,Switches:TACT_SKRP,C341730
BMI088,U1,ICs:BOSCH_LGA-16,C194919
CC2500,U2,ICs:TI_QFN-20,C57494
M24C32,U3,ICs:STM_SO8N,C79920
BMP388,U4,ICs:BOSCH_LGA-10,C779278
SN65HVD232D,"U5,U6",ICs:TI_SOIC-8,C30530
LIS3MDL,U7,ICs:STM_LGA-12L,C478483
LM2672,U8,ICs:TI_SOIC-8,C180371
TPS79633,U9,ICs:TI_SOT223-6,C485803
STM32G474CET6,U10,ICs:STM_LQFP48,C730125
NX2520SA-26MHz,X1,CrystalsAndOscillators:NDK_NX2520SA,C910046
NX2520SA-16MHz,X2,CrystalsAndOscillators:NDK_NX2520SA,C280836
